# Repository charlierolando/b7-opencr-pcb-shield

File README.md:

# b7-opencr-pcb-shield

>This is the OpenCR PCB design that we used to participate in KRSTI 2023

>Top View. Click [this](https://github.com/charlierolando/b7-opencr-pcb-shield/blob/main/images/Top%20View.png) when the image doesn't appear

>Bottom View. Click [this](https://github.com/charlierolando/b7-opencr-pcb-shield/blob/main/images/Bottom%20View.png) when the image doesn't appear

<br></br>

>Preview View. Click [this](https://github.com/charlierolando/b7-opencr-pcb-shield/blob/main/images/Preview.png) when the image doesn't appear

## [In Collaboration with:](#in-collaboration-with)

[Charlie Rolando](https://github.com/charlierolando)

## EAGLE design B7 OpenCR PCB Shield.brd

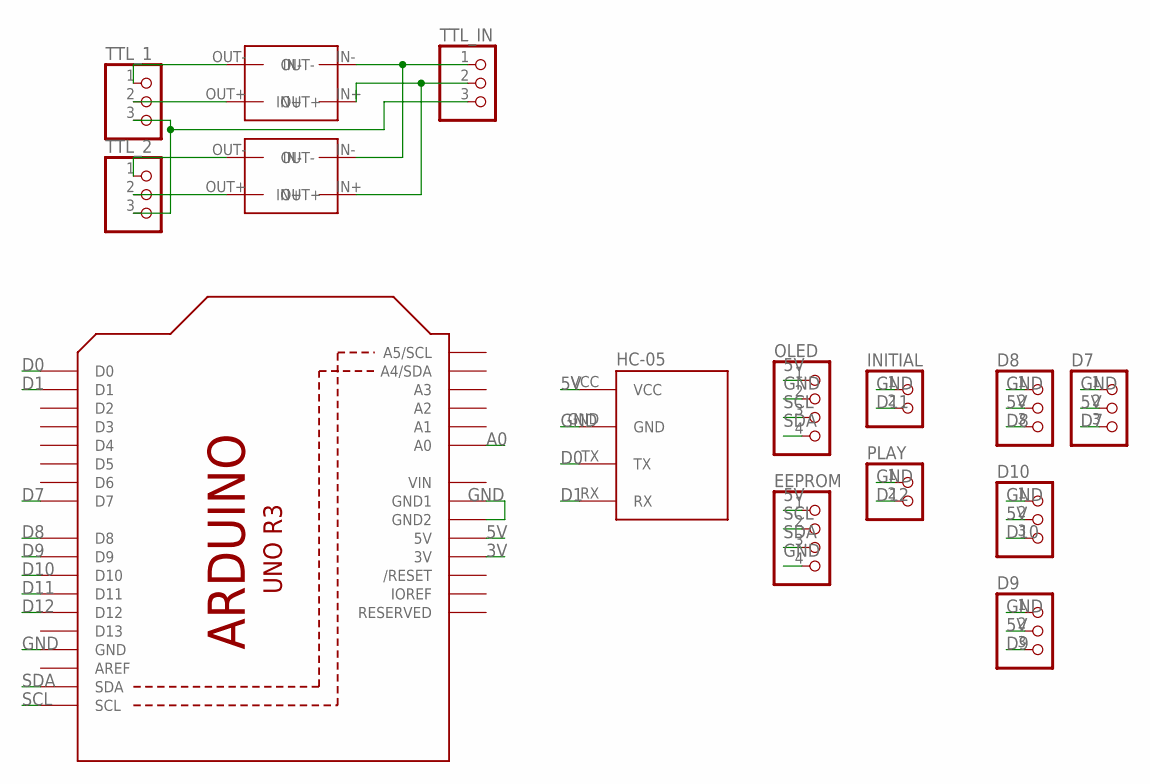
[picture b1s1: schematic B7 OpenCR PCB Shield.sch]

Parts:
D7, D8, D9, D10: PINHD-1X3; 1X03
EEPROM: PINHD-1X4; 1X04
HC-05: BLUETOOTH_BOARD; BT_BOARD_FOOTPRINT
INITIAL: PINHD-1X2; 1X02
OLED: PINHD-1X4; 1X04
PLAY: PINHD-1X2; 1X02
TTL_1, TTL_2: PINHD-1X3; 1X03
TTL_IN: PINHD-1X3; 1X03
U2: ARDUINOR3-BPLACE
U$1, U$2: LM2596LM2596; LM2596

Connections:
3V: U2.3V
5V: D7.2, D8.2, D9.2, D10.2, EEPROM.1, HC-05.VCC, OLED.1, U2.5V
A0: U2.A0
D0: HC-05.TX, U2.D0
D1: HC-05.RX, U2.D1
D7: D7.3, U2.D7
D8: D8.3, U2.D8
D9: D9.3, U2.D9
D10: D10.3, U2.D10
D11: INITIAL.2, U2.D11
D12: PLAY.2, U2.D12
GND: D7.1, D8.1, D9.1, D10.1, EEPROM.4, HC-05.GND, INITIAL.1, OLED.2, PLAY.1, U2.GND, U2.GND1, U2.GND2
unnamed: TTL_IN.1, U$1.IN-, U$2.IN-
unnamed: TTL_IN.2, U$1.IN+, U$2.IN+
unnamed: TTL_1.3, TTL_2.3, TTL_IN.3
unnamed: TTL_1.2, U$1.OUT+
unnamed: TTL_2.2, U$2.OUT+
unnamed: TTL_1.1, U$1.OUT-
unnamed: TTL_2.1, U$2.OUT-
SCL: EEPROM.2, OLED.3, U2.SCL
SDA: EEPROM.3, OLED.4, U2.SDA
VIN: U2.VIN

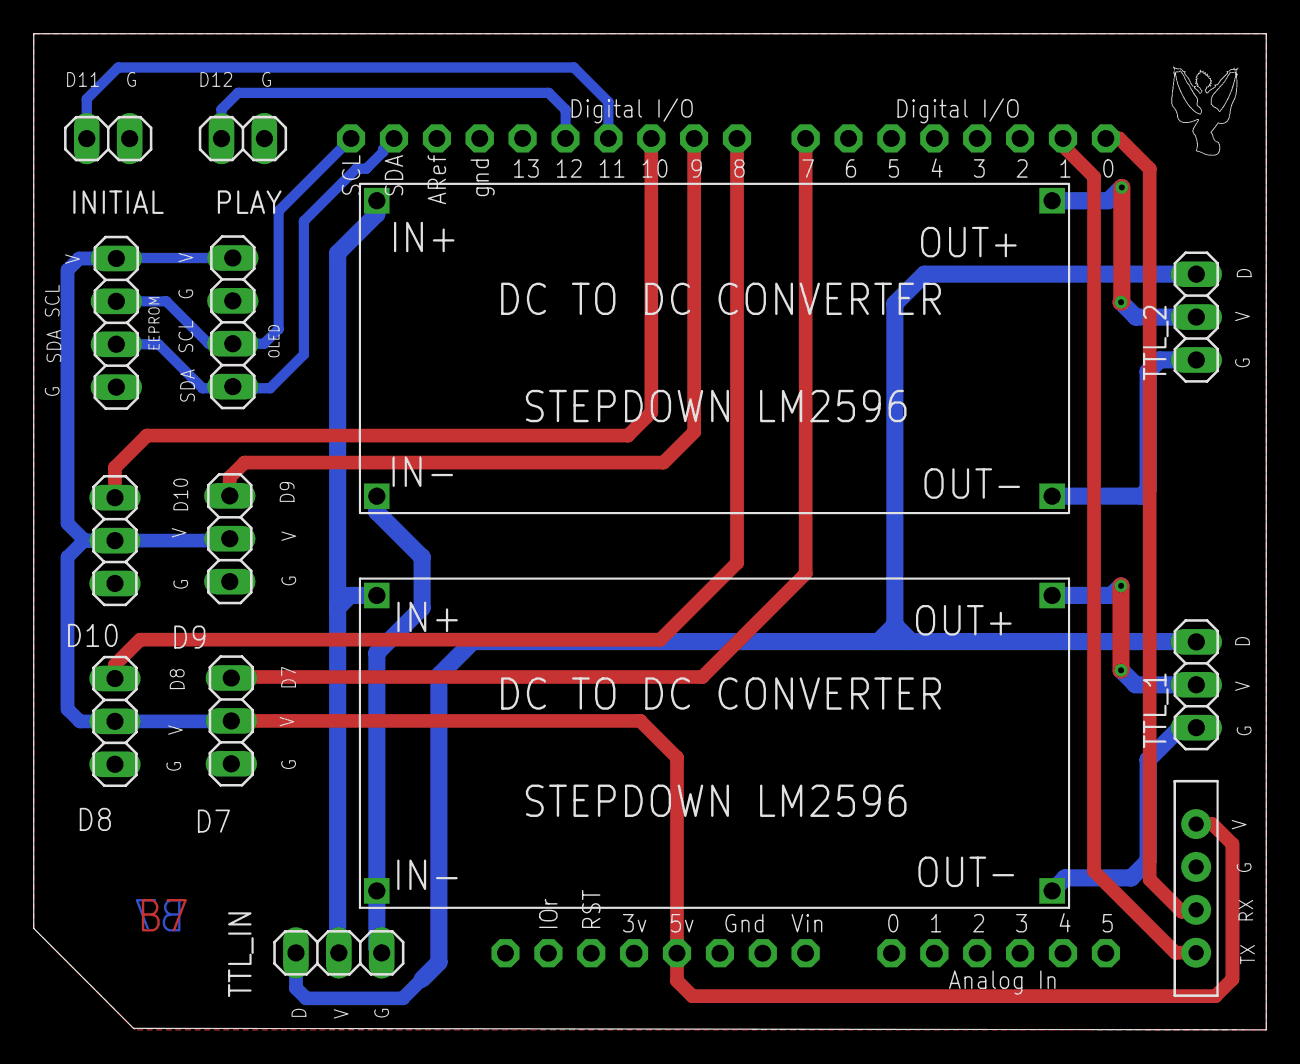
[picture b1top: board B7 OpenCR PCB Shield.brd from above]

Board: 2 copper layers, 73.0 x 59.0 mm, 15 parts (0 on the bottom side), 19 nets.
